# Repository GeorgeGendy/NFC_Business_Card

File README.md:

# NFC_Business_Card
NFC Business Card 
Two versions are included:

* One version uses standard layers (top, bottom, silk screen, tstop, etc).
* The other version mainly uses traces and does not need silk screen layer in case all what can be done is just milling the board. In this version, the LED is placed on the map, which is made of traces on the bottom layer. This version is not tested thought.

Smart phone app or tool can be used to program the NFC chip, assuming that the smart phone has NFC capabilities.

Attribute: https://www.instructables.com/PCB-Business-Card-With-NFC/

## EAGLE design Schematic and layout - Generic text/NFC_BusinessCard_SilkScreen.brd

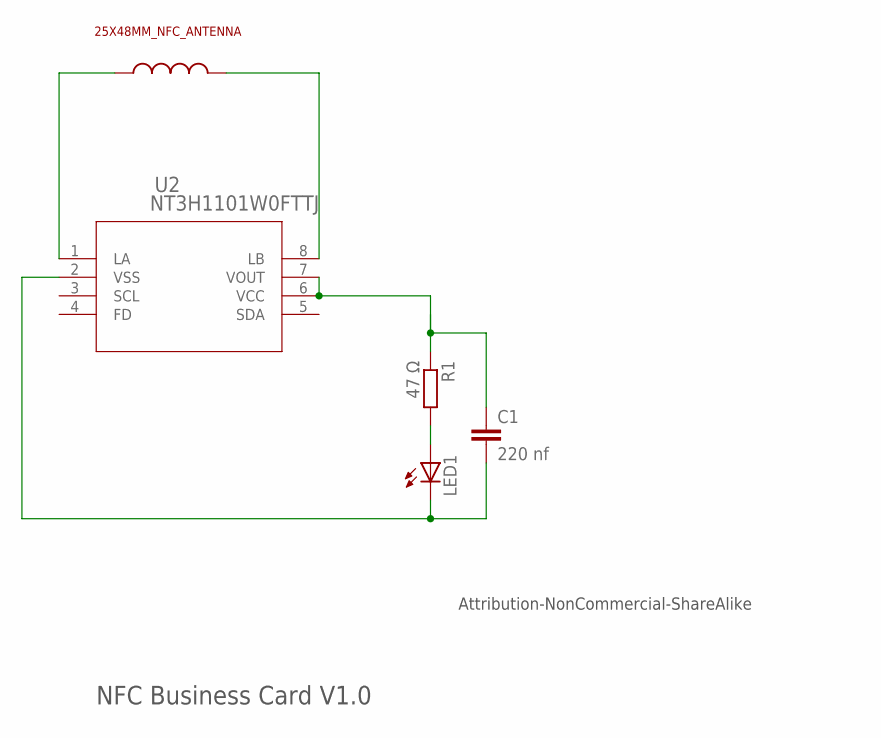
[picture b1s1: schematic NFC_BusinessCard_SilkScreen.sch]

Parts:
ANT: 25X48MM_NFC_ANTENNA; 25X48MM_NFC
C1: 220 nf; C0603
LED1: LEDSML0805; SML0805
R1: 47 Ω; R0603
U2: NT3H1101W0FTTJ; TSSOP8_SOT505-1_NXP

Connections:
unnamed: ANT.P$1, U2.8 (LB)
unnamed: C1.2, LED1.C, U2.2 (VSS)
unnamed: ANT.P$2, U2.1 (LA)
unnamed: LED1.A, R1.2
unnamed: C1.1, R1.1, U2.6 (VCC), U2.7 (VOUT)

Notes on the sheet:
NFC Business Card V1.0
Attribution-NonCommercial-ShareAlike

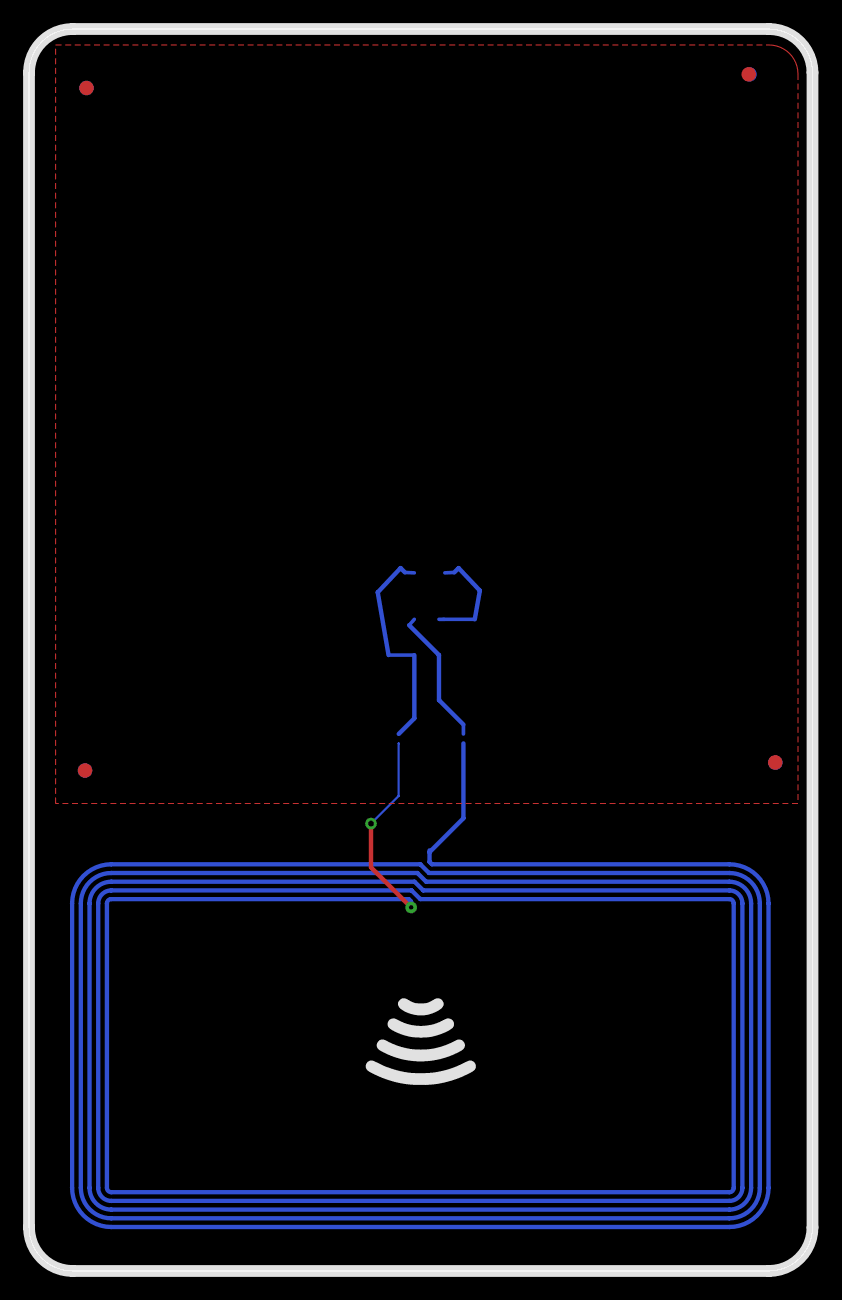
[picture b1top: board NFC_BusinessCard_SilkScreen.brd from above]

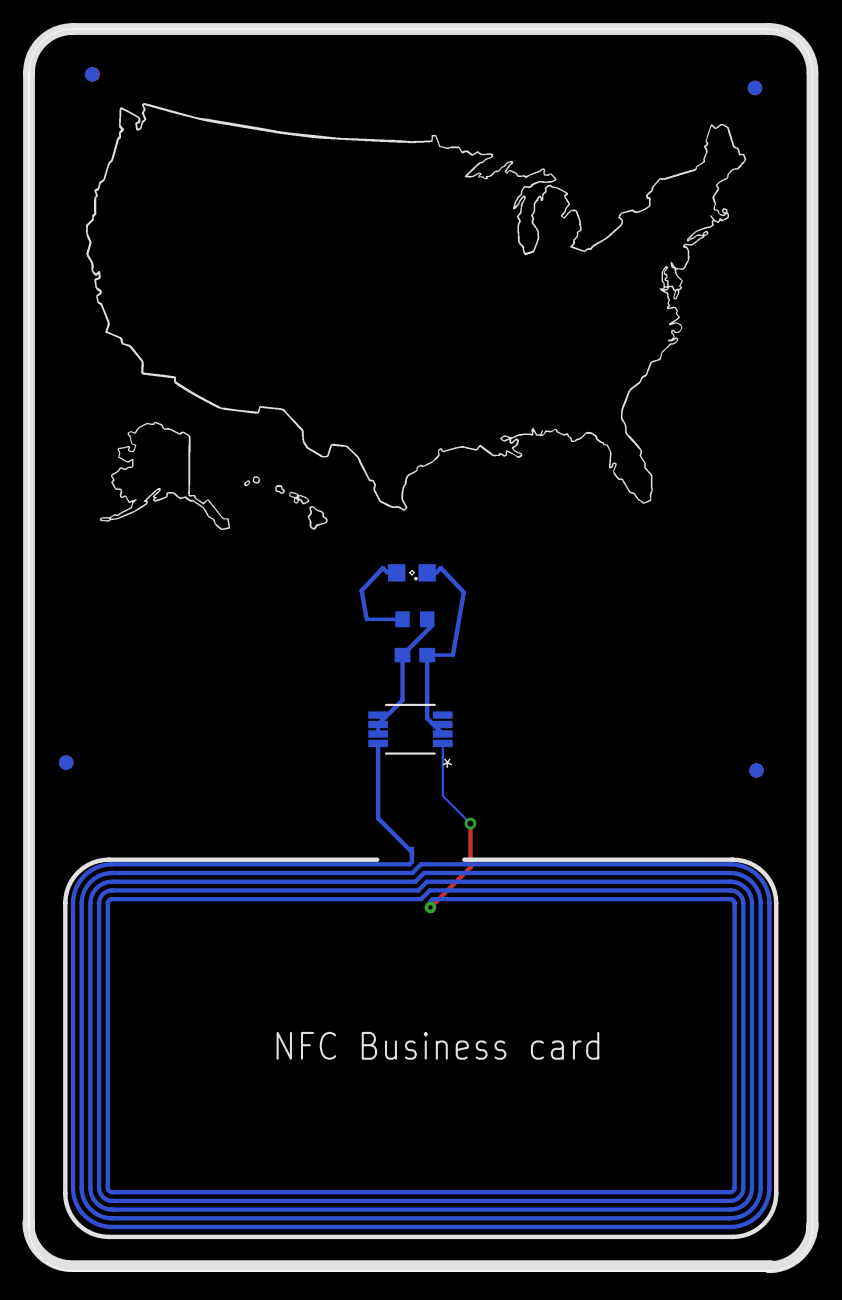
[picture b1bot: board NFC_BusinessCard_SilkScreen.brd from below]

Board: 2 copper layers, 54.0 x 85.6 mm, 13 parts (9 on the bottom side), 5 nets.

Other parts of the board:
U$1, U$2, U$3, U$4, U$5, U$6, U$7, U$8: FIDUCIAL_G10

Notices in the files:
parts and their libraries:
dicons: Copyright (C) 2004, Bob Starr (rtzaudio@mindspring.com)
COPYRIGHT: Copyright (C) 2023 Ultra Librarian. All rights reserved.
